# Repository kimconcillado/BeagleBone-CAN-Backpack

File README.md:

BeagleBone-CAN-Backpack
=======================

The BeagleBone CAN backpack plugs into a BeagleBone and provides a CAN transceiver and +12V power.

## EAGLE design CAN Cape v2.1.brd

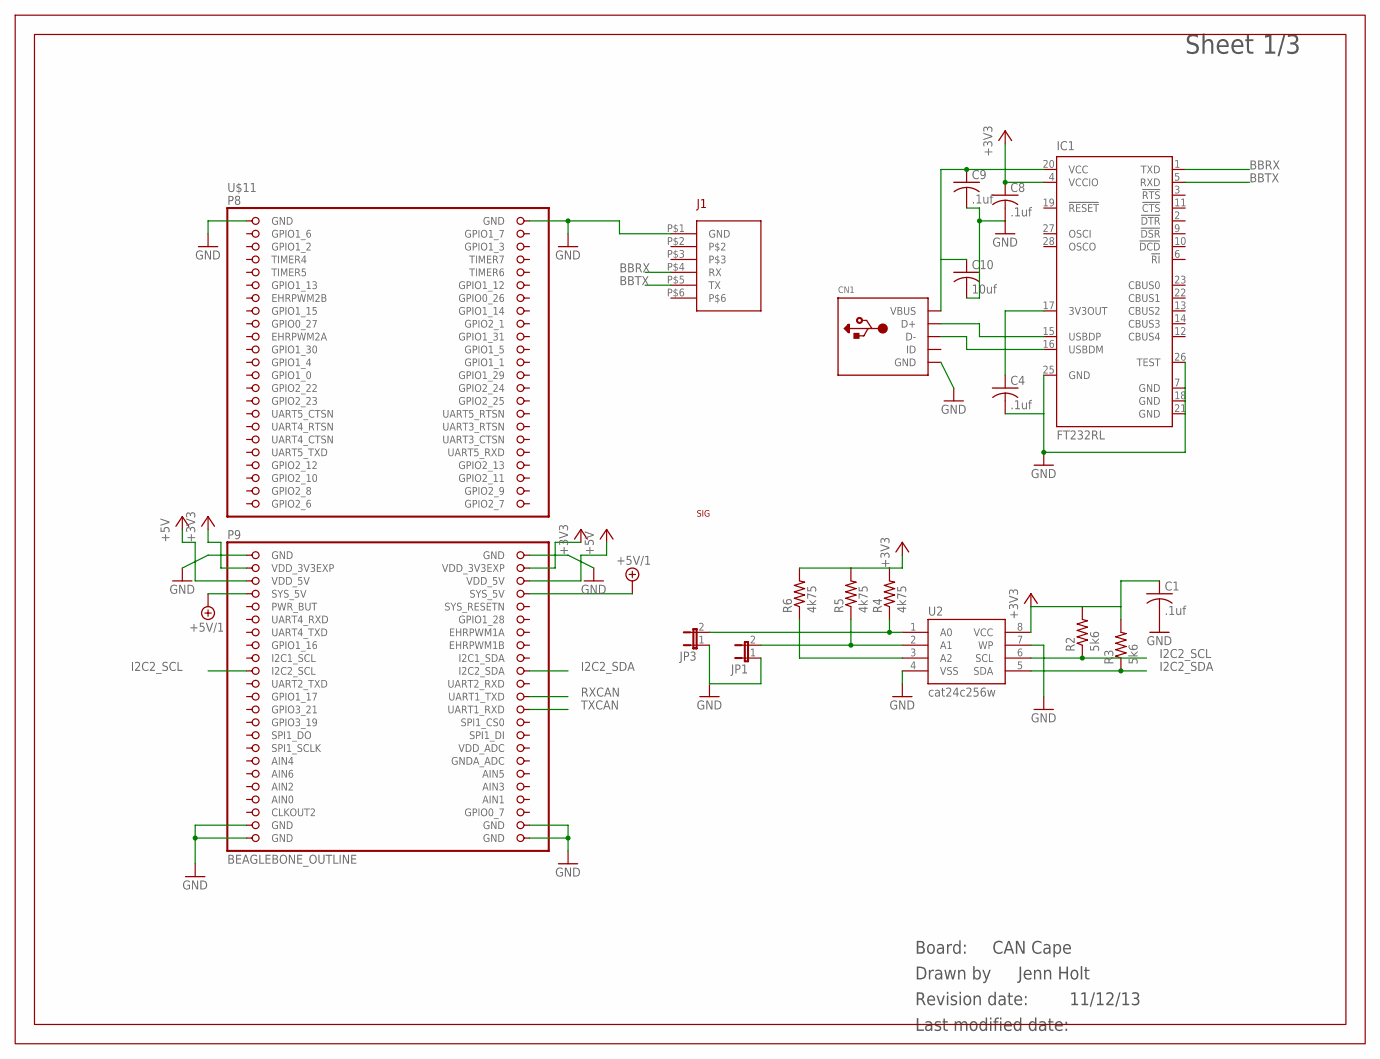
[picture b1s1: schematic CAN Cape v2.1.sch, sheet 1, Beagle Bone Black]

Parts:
C1, C4, C8, C9: .1uf; C0603; PARTNO C1608X7R1E104K080AA
C10: 10uf; C0805; PARTNO GRM21BR61C106KE15L
CN1: USBMINIB; USB-MINIB; PARTNO 1734035-2
IC1: FT232RL; SSOP28; PARTNO FT232RL
JP1, JP3: JUMPER-2SMD-NO; SJ_2S-NO
R2, R3: 5k6; R0603; PARTNO ERJ-3EKF4701V
R4, R5, R6: 4k75; R0603; PARTNO ERJ-3EKF4701V
U2: cat24c256w; SO08; PARTNO CAT24C256WI-GT3
U$5: SIG
U$10: CURRENT-C-LETTER-LANDSCAPE; BLANK
U$11: BEAGLEBONE_OUTLINE; BEAGLEBONE_SHIELD

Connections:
+3V3: C1.1, C8.1, IC1.4 (VCCIO), R2.2, R3.2, R4.2, R5.2, R6.2, U2.8 (VCC), U$11.49 (VDD_3V3EXP), U$11.50 (VDD_3V3EXP); also elsewhere on the board
+5V: U$11.51 (VDD_5V), U$11.52 (VDD_5V); also elsewhere on the board
+5V/1: U$11.53 (SYS_5V), U$11.54 (SYS_5V)
A0: JP3.2, R4.1, U2.1 (A0)
A1: JP1.2, R5.1, U2.2 (A1)
AIN0: U$11.85 (AIN0)
BBRX: IC1.1 (TXD), U$11.P$4 (RX)
BBTX: IC1.5 (RXD), U$11.P$5 (TX)
GND: C1.2, C4.2, C8.2, C9.2, C10.2, CN1.GND, IC1.7 (GND), IC1.18 (GND), IC1.21 (GND), IC1.25 (GND), IC1.26 (TEST), JP1.1, JP3.1, U2.4 (VSS), U2.7 (WP), U$11.1 (GND), U$11.2 (GND), U$11.47 (GND), U$11.48 (GND), U$11.89 (GND), U$11.90 (GND), U$11.91 (GND), U$11.92 (GND), U$11.P$1 (GND); also elsewhere on the board
I2C2_SCL: R2.1, U2.6 (SCL), U$11.65 (I2C2_SCL)
I2C2_SDA: R3.1, U2.5 (SDA), U$11.66 (I2C2_SDA)
unnamed: C9.1, C10.1, CN1.VBUS, IC1.20 (VCC)
unnamed: CN1.D+, IC1.15 (USBDP)
unnamed: CN1.D-, IC1.16 (USBDM)
unnamed: R6.1, U2.3 (A2)
unnamed: C4.1, IC1.17 (3V3OUT)
RXCAN: U$11.70 (UART1_TXD); also elsewhere on the board
TXCAN: U$11.72 (UART1_RXD); also elsewhere on the board

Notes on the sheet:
Jenn Holt
CAN Cape
11/12/13

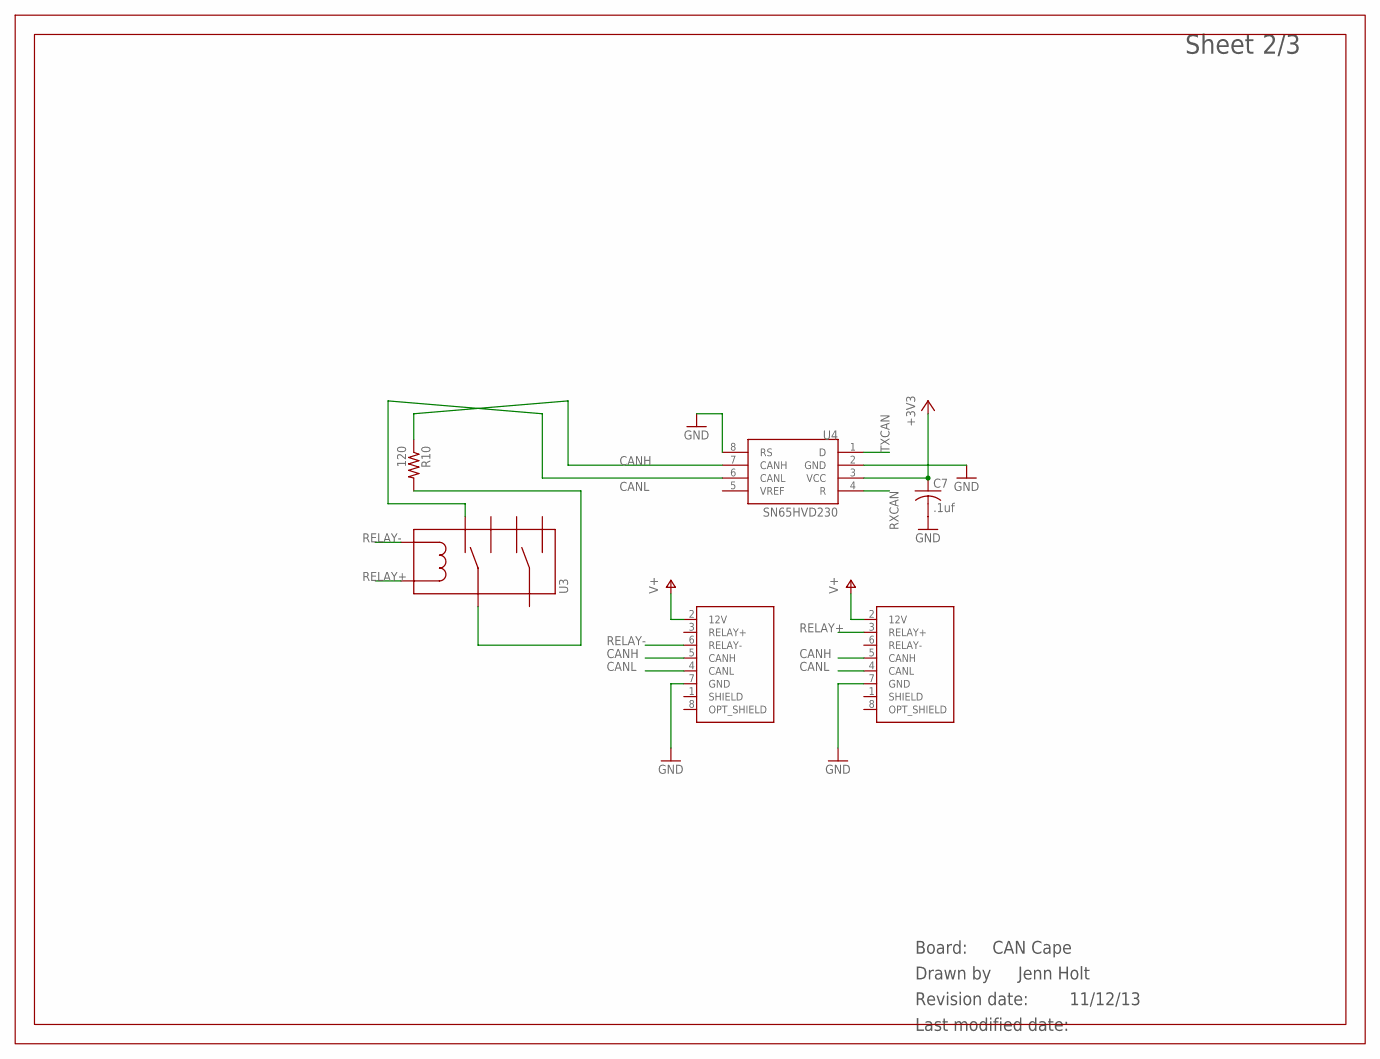
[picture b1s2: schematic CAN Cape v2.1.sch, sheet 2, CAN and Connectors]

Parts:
C7: .1uf; C0603; PARTNO C1608X7R1E104K080AA
R10: 120; R0603; PARTNO RC0805FR-07120RL
U3: IM_RELAY; PARTNO IM26GR
U4: SN65HVD230; SOIC8; PARTNO SN65HVD230D
U$6, U$7: CANBUS2VERT; 776276-1_AMPSEAL_8_VERT; PARTNO 1-776276-1
U$9: CURRENT-C-LETTER-LANDSCAPE; BLANK

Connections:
+3V3: C7.1, U4.3 (VCC); also elsewhere on the board
CANH: R10.1, U4.7 (CANH), U$6.5 (CANH), U$7.5 (CANH)
CANL: U3.2 (NC1), U4.6 (CANL), U$6.4 (CANL), U$7.4 (CANL)
GND: C7.2, U4.2 (GND), U4.8 (RS), U$6.7 (GND), U$7.7 (GND); also elsewhere on the board
unnamed: R10.2, U3.3 (COM1)
RELAY+: U3.1 (C1), U$7.3 (RELAY+)
RELAY-: U3.8 (C2), U$6.6 (RELAY-)
RXCAN: U4.4 (R); also elsewhere on the board
TXCAN: U4.1 (D); also elsewhere on the board
V+: U$6.2 (12V), U$7.2 (12V); also elsewhere on the board

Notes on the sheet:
Jenn Holt
CAN Cape
11/12/13

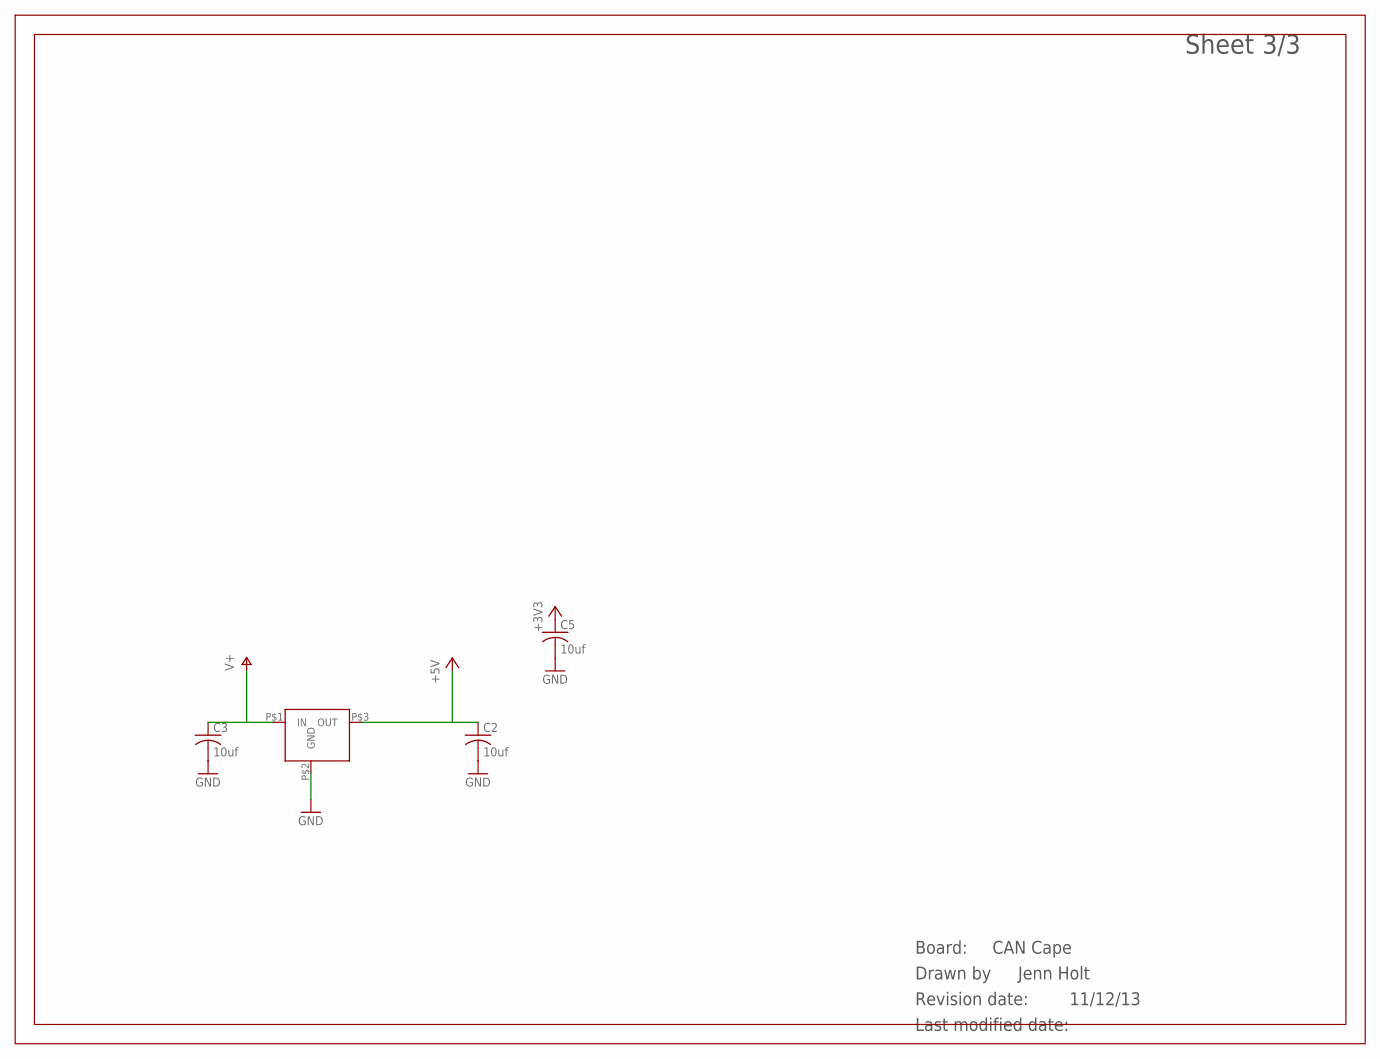
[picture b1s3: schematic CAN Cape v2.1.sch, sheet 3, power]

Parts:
C2, C3, C5: 10uf; C0805; PARTNO GRM21BR61C106KE15L
U1: RECOM_DCDC; INNOLINE-SIP; PARTNO R-78C5.0-1.0
U$4: CURRENT-C-LETTER-LANDSCAPE; BLANK

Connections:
+3V3: C5.1; also elsewhere on the board
+5V: C2.1, U1.P$3 (OUT); also elsewhere on the board
GND: C2.2, C3.2, C5.2, U1.P$2 (GND); also elsewhere on the board
V+: C3.1, U1.P$1 (IN); also elsewhere on the board

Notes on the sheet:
Jenn Holt
CAN Cape
11/12/13

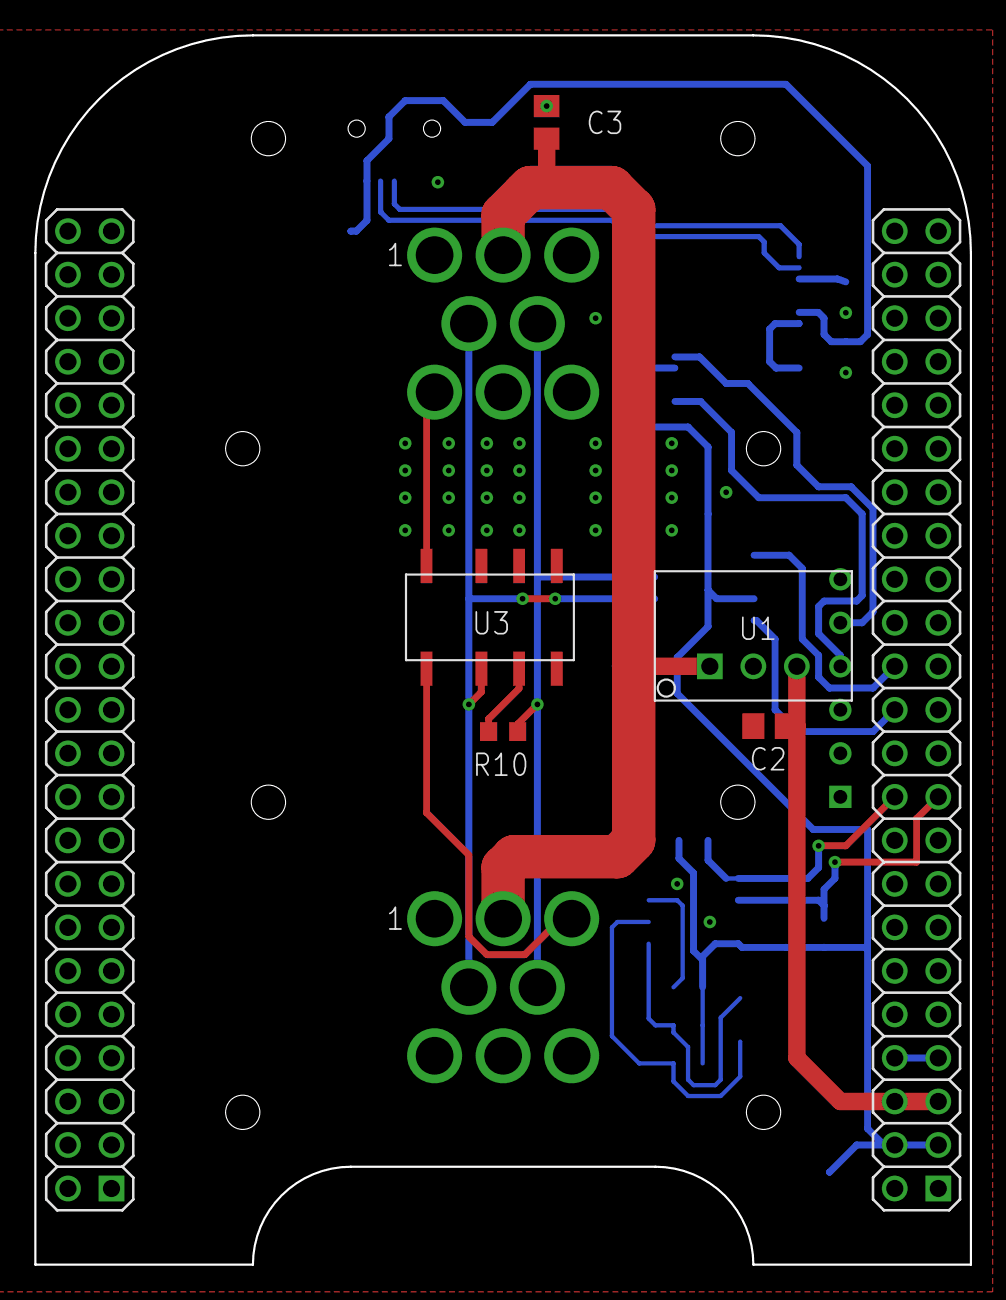
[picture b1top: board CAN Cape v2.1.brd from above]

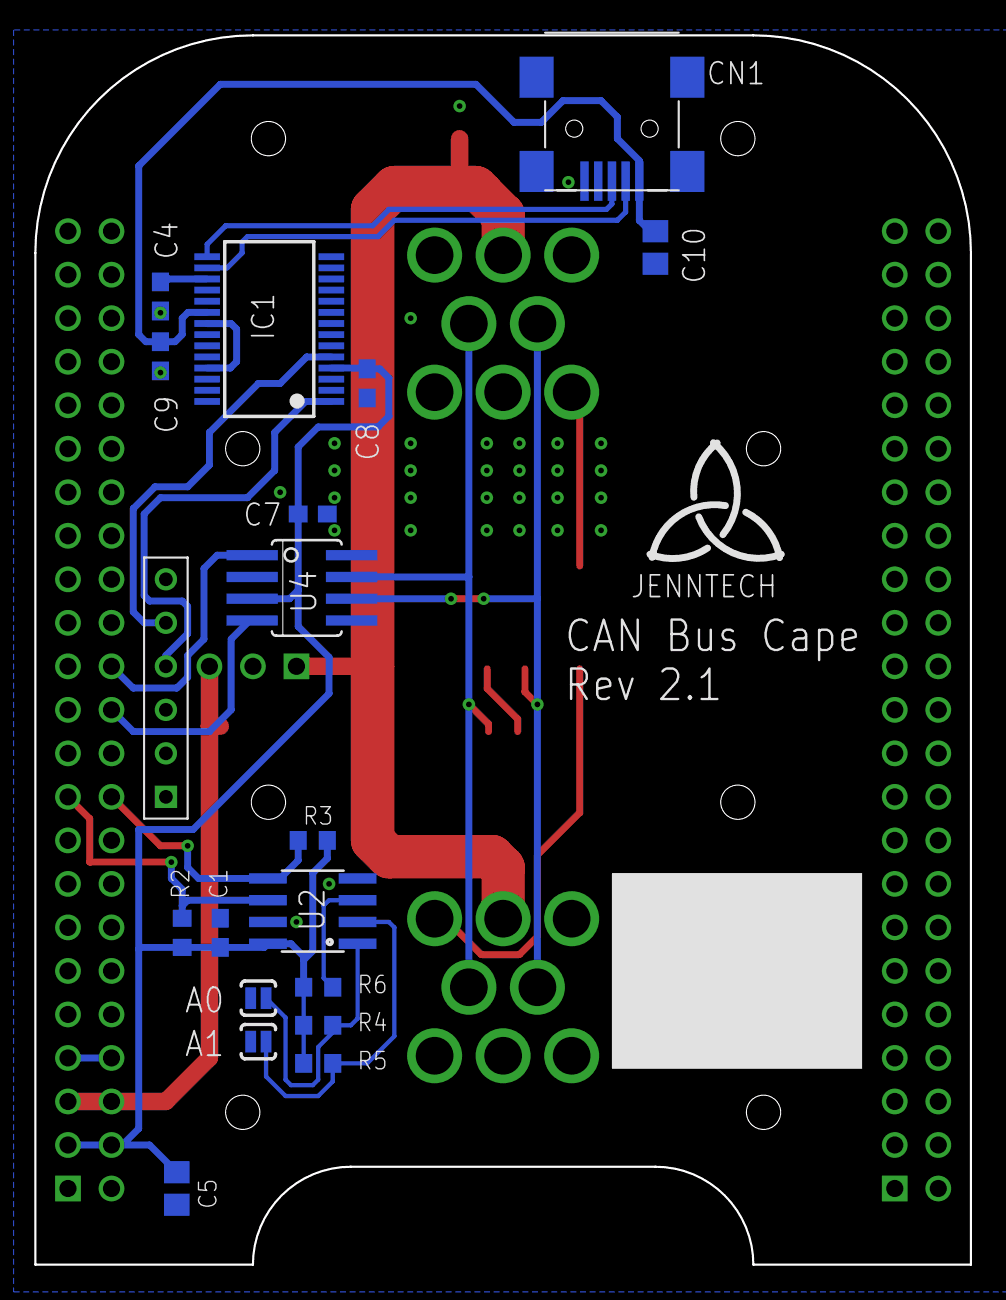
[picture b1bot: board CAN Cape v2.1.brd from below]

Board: 2 copper layers, 54.6 x 71.8 mm, 30 parts (19 on the bottom side), 23 nets.

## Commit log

2015-01-19 Move version 2.1 into GitHub
2015-01-25 Created schematic, removed files from last revision of board
2015-02-03 Revert "Working changes for v2.2"
2015-02-03 added ICs to schematic, began board arrangement
2015-02-05 Arranged components on board, updated schematic with updated components
2015-02-08 finished hooking up pads with routes/polygons/vias
2015-02-10 edited board
2015-02-11 More werk
2015-02-12 Board is DRC approved, schematic is ERC approved
2015-02-17 PUT LABELS ON IT, MADE A BOM
2015-02-17 Added necessary documentation
2015-02-25 RXCAN and TXCAN were switched per Jenn's suggested fix
2015-02-25 recreated gerbers and sch pdf
2015-02-26 Recreate changelog.txt and README.md (seem to have accidentally been deleted in f57f23)
2015-02-26 Approve rogue "Dimension" error on .brd (mechanical pad too near radius of board).
2015-02-26 Add version number and revision date to schematic. Regenerate pdf files.
2015-03-27 Resolved Issue #8 Duplicate lines in BOM
2015-03-27 Resolved Issue #10 USB connection pinout error
2015-03-30 Resolved issue #10 USB pinout error by updating Components library
2015-03-31 Preliminary LED driver circuit implemented for issue #13 Add LED driver circuit for front panel indicator LEDs
2015-04-02 Named nets and connected to pins for issue #13
2015-04-02 Added connector for issue #15
2015-04-02 Added power circuit for #14
2015-04-04 Passes DRC (as long as polygon width errors are neglegible) and ERC
2015-04-04 Commit containing changes from Aaron and Sean. Still have to :change wake signal to GPIO set 0, name connectors, rename pin nets connected to LEDs , label connectors
2015-04-06 BOM created, passes ERC and DRC
2015-04-06 Made PDFs
2015-04-06 Completed BOM with categories and unit price
2015-04-06 Gerbers created BITCH
2015-04-07 Ignore Excel temp files
2015-04-07 Add version number to sch. Update connector labeling from Molex.lbr. Regenerate PDFs.
2015-05-13 TX and RX CAN lines are routed, Unrouted layer is on
2015-05-14 rerouted new pins for LEDs, check out shaky DRC because coffee shop is closing and I have to go
2015-05-15 Update with corrected transistor packages from Component-libraries. Correct board layout to reflect updated footprints.
2015-05-15 Ignore junk files
2015-05-15 Resolve DRC errors
2015-05-15 Bump version number to v2.3.1; regenerate Gerbers/PDFs
2015-05-15 Ignore Gerber junk
2015-05-15 Can't figure out how to merge/pull stuff from Github to PC so I'm creating new gerbers for myself

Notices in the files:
parts and their libraries:
SparkFun: Licensing: CC v3.0 Share-Alike You are welcome to use this library for commercial purposes.
